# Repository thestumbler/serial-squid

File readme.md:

## Synopsis

The Serial Squid is a serial communications hub, useful for the development and testing of embedded systems projects. It can be operated stand-alone or remotely. True to its namesake, the Serial Squid has eight arms, two tentacles, and a round body. The I/O ports are found on the appendages, and the user interface and other supporting circuitry is found on the head and main body.

More information about the project can be found on my blog and project pages.

* [thestumbler](http://thestumbler.github.io)
* [theserialsquid](http://thestumbler.github.io/serial-squid/)

## Project File Organization

#### Key Files of Interest

* Bill of Materials:  docs/squid-bom.ods / .xlsx
* Block Diagram: docs/squid-block-diag.odg / .pdf
* LPC1769 Pinout Chart:  docs/squid-pinouts.ods / .xlsx
* Mechanical Drawing: mech/pcb_squid.dwg
* Parts Datasheets: parts/
* KiCAD Schematics, PCB files: sch/

## Status

* BOM is 98% completed.  All parts can be procured from DigiKey.  One problem has been sourcing a SMT 2x3 shrouded box header.

* Schematics 98% completed.  A few minor changes to be made, have been postponed until preliminary routing of the board is completed.  I want to see how much free room is remaining before deciding on the final few schematic changes.

* PCB first draft parts placement completed.  Routing will start after one more pass over the placement.

## github TODO

Add OpenSCAD 3D source code, which gives an fairly realistic mock-up of the final assembly.  It all works, but I need to re-organize some modules.  For example, many non-header parts reside in the header module.  Also, I need to sort out how to make a fork of another project, since I built my OpenSCAD library of parts upon a pre-existing library.

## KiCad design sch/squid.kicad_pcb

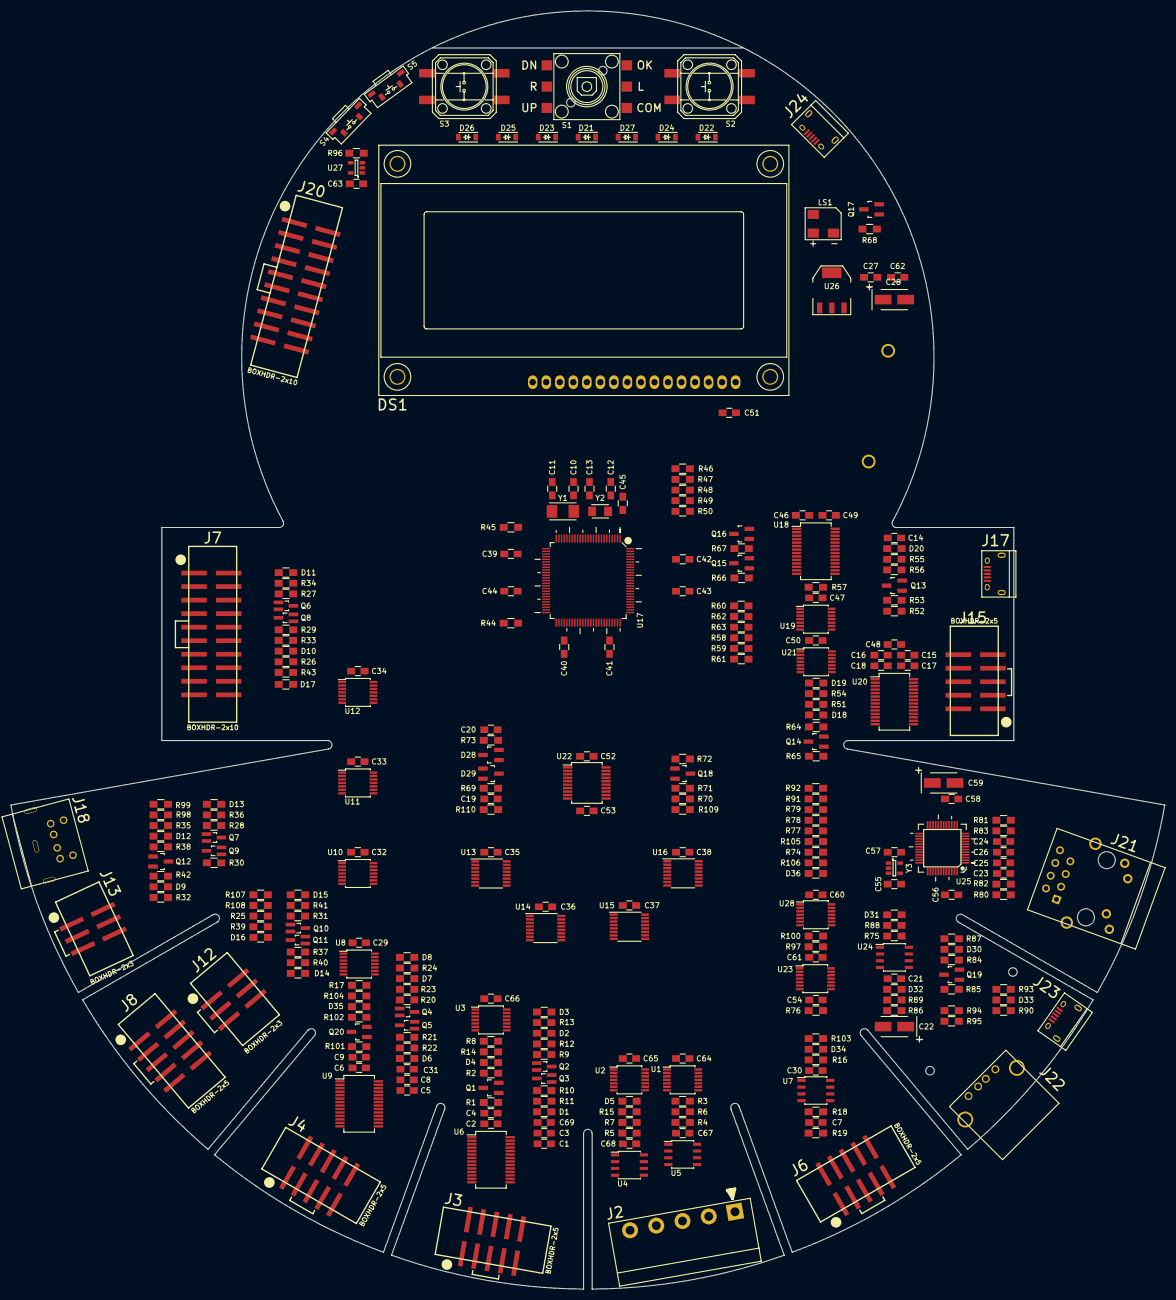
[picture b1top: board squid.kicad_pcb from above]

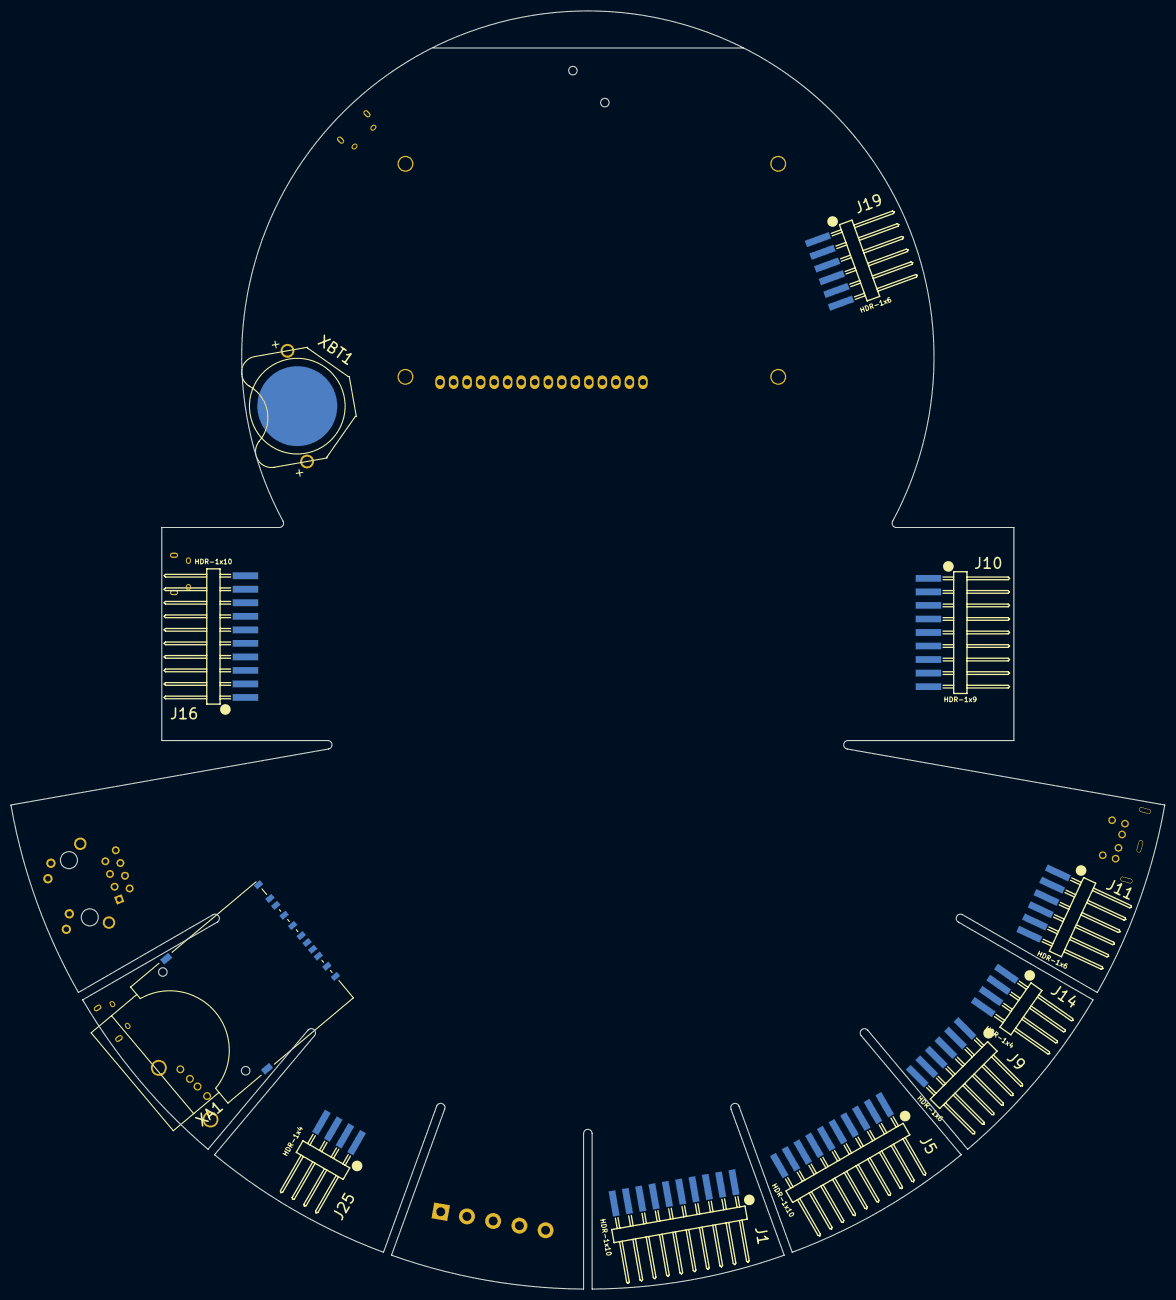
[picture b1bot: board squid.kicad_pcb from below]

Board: 2 copper layers, 216.7 x 240.0 mm, 300 parts (11 on the bottom side), 278 nets, no tracks yet.

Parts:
C1, C2, C3, C4, C5, C6, C8, C9, C14, C15, C16, C17, C18, C21, C23, C24, C25, C26, C29, C30, C31, C32, C33, C34, C35, C36, C37, C38, C40, C41, C42, C43, C44, C45, C46, C47, C48, C49, C50, C51, C52, C53, C54, C55, C56, C57, C58, C60, C61, C62, C63, C64, C65, C66, C67, C68, C69: 0.1uF; C_0805_HandSoldering
C7: 0.001uF; C_0805_HandSoldering
C10, C11, C12, C13: 18pF; C_0805_HandSoldering
C19, C20: 0.47uF; C_0805_HandSoldering
C22, C28, C59: 10uF; TantalC_SizeB_EIA-3528_HandSoldering
C27, C39: 1.0uF; C_0805_HandSoldering
D1, D2, D3, D4, D5, D6, D7, D8, D9, D10, D11, D12, D13, D14, D15, D16, D17, D18, D19, D20, D30, D31, D32, D33, D34, D35, D36: LED-GREEN; R_0805_HandSoldering
D21, D22, D23, D24, D25, D26, D27: 1N4148; SOD-123
D28, D29: BAT54; SOT-23_Handsoldering
DS1: LCD-4x20; NHD-0420AZ
J1, J5, J16: HDR-1x10; PHDR-RA-SMT-1x10
J2: TERM-BLOCK-5; term-block-5
J3, J4, J6, J8, J15: BOXHDR-2x5; SHDR-SMT-2x5
J7, J20: BOXHDR-2x10; SHDR-SMT-2x10
J9, J11, J19: HDR-1x6; PHDR-RA-SMT-1x6
J10: HDR-1x9; PHDR-RA-SMT-1x9
J12, J13: BOXHDR-2x3; SHDR-SMT-2x3
J14, J25: HDR-1x4; PHDR-RA-SMT-1x4
J17, J23, J24: USB-MICRO-B; USB_Micro-B
J18: MINIDIN6; MINIDIN-RA-THRU-6
J21: RJ45-MAGS; RJ45_TRANSFO_PULSE_A
J22: USB-TYPE-A; USB_A
LS1: BUZZER; BUZZER-CSS-0575A
Q1, Q12, Q13, Q14, Q15, Q16, Q17, Q20: 2N3904; SOT-23-BEC-HAND
Q2, Q3, Q4, Q5, Q6, Q7, Q8, Q9, Q10, Q11: DMG1013; SOT-323-GSD-HAND
Q18: 2N2222; SOT-23-BEC-HAND
Q19: 2N3906; SOT-23-BEC-HAND
R1, R38, R56, R65, R66, R67, R68, R72, R73, R84, R101: 1K; R_0805_HandSoldering
R2, R3, R4, R5, R6, R7, R8, R9, R10, R16, R17, R20, R21, R25, R26, R27, R28, R29, R30, R31, R37, R44, R45, R46, R47, R48, R49, R50, R53, R57, R58, R59, R60, R61, R62, R63, R64, R69, R70, R71, R74, R75, R76, R77, R78, R79, R96, R97, R100, R102, R105: 10K; R_0805_HandSoldering
R11, R12, R13, R14, R15, R22, R23, R24, R32, R33, R34, R35, R36, R39, R40, R41, R43, R51, R54, R55, R87, R88, R89, R90, R91, R92, R93, R103, R104, R106: 220; R_0805_HandSoldering
R18, R19: 60; R_0805_HandSoldering
R42: 20K; R_0805_HandSoldering
R52, R98, R99, R107, R108, R109, R110: 4.7K; R_0805_HandSoldering
R80, R81, R82, R83: 49.9; R_0805_HandSoldering
R85: 1.5K; R_0805_HandSoldering
R86: 100K; R_0805_HandSoldering
R94, R95: 15K; R_0805_HandSoldering
S1: SW_NAVI; SW_NAVI_JS5208
S2, S3: SW_PUSH; SW_PBUTTON_TL330
S4, S5: SW_PUSH_RA; SW_SPSW_TACT_RA
U1, U2, U3, U8, U10, U11, U12, U19, U21, U23, U28: 74HCT4066; TSSOP-14_4.4x5mm_Pitch0.65mm
U4, U5: SN75176B; SOIC-8_3.9x4.9mm_Pitch1.27mm
U6, U9, U20: MAX3241E; SSOP-28_5.3x10.2mm_Pitch0.65mm
U7: TJA1040; SOIC-8_3.9x4.9mm_Pitch1.27mm
U13, U14, U15, U16: 74HCT595; TSSOP-16_4.4x5mm_Pitch0.65mm
U17: LPC1769; LQFP-100_14x14mm_Pitch0.5mm
U18: FT232R; SSOP-28_5.3x10.2mm_Pitch0.65mm
U22: PIC16F1847; SSOP-20_5.3x7.2mm_Pitch0.65mm
U24: LM3526-L; SOIC-8_3.9x4.9mm_Pitch1.27mm
U25: DP83848; PQFP48-14x14mm
U26: MIC39100-3.3; SOT-223
U27: MCP1322; SOT-23-5
XA1: SD-SOCKET; SD_Card_Receptacle
XBT1: CR2032-SOCKET; SOCKET-SMT-CR2032-KEYSTONE-3003
Y1: 12MHz; Crystal_SMD_5032_2Pads
Y2: 32.768KHz; Crystal_SMD_3215_2Pads
Y3: 50MHz; SOT-23-5

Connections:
+3V3: C23.1, C24.1, C28.1, C31.2, C39.1, C40.1, C41.1, C42.1, C43.1, C44.1, C45.1, C46.2, C48.1, C52.1, C53.2, C55.1, C56.2, C57.2, C58.1, C59.1, C60.1, C61.1, C62.1, C63.1, C69.2, D2.2, D7.2, D11.2, D13.2, D15.2, D29.2, J20.1, J20.2, Q2.S, Q4.S, Q6.S, Q7.S, Q10.S, R2.1, R4.1, R9.1, R20.1, R27.1, R28.1, R31.1, R44.1, R45.1, R47.1, R48.1, R49.1, R50.1, R58.1, R59.1, R60.1, R61.1, R62.1, R63.1, R64.1, R69.1, R74.2, R77.2, R78.2, R79.2, R80.1, R81.1, R82.2, R83.2, R91.2, R92.2, R96.1, R97.1, R98.1, R99.1, R100.1, R102.1, R105.2, R109.1, R110.1, U6.26, U9.26, U17.10, U17.28, U17.42, U17.54, U17.71, U17.84, U17.96, U18.4, U20.26, U22.15, U22.16, U25.22, U25.32, U25.48, U26.3, U27.5, U28.14, XA1.4, Y3.4
+5V: C21.1, C27.1, C29.1, C30.2, C32.1, C33.1, C34.1, C35.1, C36.1, C37.1, C38.1, C47.1, C49.1, C50.1, C51.2, C54.1, C64.1, C65.1, C66.1, C67.1, C68.1, D1.2, D6.2, D10.2, D12.2, D14.2, D34.2, DS1.2, DS1.15, J6.8, J18.4, J24.1, J25.1, LS1.1, Q3.S, Q5.S, Q8.S, Q9.S, Q11.S, Q19.E, R10.1, R16.2, R21.1, R29.1, R30.1, R37.1, U1.14, U2.14, U3.14, U4.8, U5.8, U7.3, U8.14, U10.14, U11.14, U12.14, U13.16, U14.16, U15.16, U16.16, U18.20, U19.14, U21.14, U23.14, U24.7, U26.1
/CFG0: R55.2, R56.2, U13.15
/CFG1: R51.2, R65.1, U13.1, U20.22
/CFG2: R54.2, R57.1, U13.2, U19.5, U19.6, U19.12, U19.13, U21.5, U21.13
/CFG3: R1.1, R14.2, U6.22, U13.3
/CFG4: R3.1, R15.2, U1.5, U1.13, U2.6, U13.4
/CFG5: R8.1, R13.2, U2.5, U2.13, U3.5, U3.6, U3.12, U3.13, U13.5
/CFG6: Q3.G, R10.2, R11.2, U13.6
/CFG7: Q2.G, R9.2, R12.2, U13.7, U14.14
/CFG8: R101.1, R104.2, U9.22, U14.15
/CFG9: R17.1, R24.2, U8.5, U8.6, U8.12, U8.13, U14.1
/CFG10: Q5.G, R21.2, R22.2, U14.2
/CFG11: Q4.G, R20.2, R23.2, U14.3
/CFG12: R16.1, R103.2, U7.8, U14.4
/CFG13: R25.1, R39.2, U10.5, U10.6, U10.12, U10.13, U11.5, U11.13, U14.5
/CFG14: Q11.G, R37.2, R40.2, U14.6
/CFG15: Q10.G, R31.2, R41.2, U14.7, U15.14
/CFG16: R26.1, R43.2, U11.6, U11.12, U12.5, U12.6, U12.12, U12.13, U15.15
/CFG17: Q8.G, R29.2, R33.2, U15.1
/CFG18: Q6.G, R27.2, R34.2, U15.2
/CFG19: R32.2, U15.3
/CFG20: Q9.G, R30.2, R35.2, U15.4
/CFG21: Q7.G, R28.2, R36.2, U15.5
/CFG22: R75.2, R88.2, U15.6, U23.5, U23.13
/CFG23: R76.2, R87.2, U15.7, U16.14, U23.6, U23.12
/CFG24: R105.1, U16.15, U25.29
/CFG25: R74.1, R106.2, U16.1, U25.7, Y3.3
/CFG26: U16.2, U28.13
/CFG27: U16.3, U28.5
/COM0/COM0B_CTS: J15.6, U20.11
/COM0/COM0B_DSR: J15.2, U20.9
/COM0/COM0B_DTR: J15.7, U20.6
/COM0/COM0B_RTS: J15.4, U20.4
/COM0/COM0B_RXD: J15.3, U20.10
/COM0/COM0B_TXD: J15.5, U20.5
/COM0/COM0C_CTSL: J16.9, U21.3
/COM0/COM0C_DSR: J16.8, U21.1
/COM0/COM0C_DTR: J16.3, U19.3
/COM0/COM0C_RTSL: J16.2, U19.1
/COM0/COM0C_RXDL: J16.7, U19.10
/COM0/COM0C_TXD: J16.4, U19.8
/COM0/COM0_CTSL: R60.2, U17.81, U18.11, U20.12, U21.4
/COM0/COM0_DSR: R62.2, U17.59, U18.9, U20.14, U21.2
/COM0/COM0_DTR: R63.2, R67.2, U17.58, U18.2, U19.4, U20.17
/COM0/COM0_RTSL: R61.2, R66.2, U17.80, U18.3, U19.2, U20.19
/COM0/COM0_RXDL: R58.2, U17.98, U18.5, U19.11, U20.13
/COM0/COM0_TXDL: R59.2, U17.99, U18.1, U19.9, U20.18
/COM0/~RESET: C19.1, D28.1, J20.15, Q16.C, R45.2, R69.2, U17.17, U27.1
/COM1/COM1C_CTSL: J1.9, U3.4
/COM1/COM1C_DSR: J1.8, U3.2
/COM1/COM1C_DTR: J1.3, U2.4
/COM1/COM1C_RTSL: J1.2, U2.2
/COM1/COM1C_RXDL: J1.7, U3.11
/COM1/COM1C_TXD: J1.4, U3.9
/COM1/COM1_CTSL: U3.3, U6.16, U17.73
/COM1/COM1_DCDL: U6.19, U17.70
/COM1/COM1_DSRL: U3.1, U6.18, U17.69
/COM1/COM1_DTRL: U2.3, U2.9, U6.12, U17.68
/COM1/COM1_RIL: U6.15, U17.67
/COM1/COM1_RTSL: U1.2, U1.3, U2.1, U6.14, U17.66
/COM1/COM1_RXDL: U3.10, U5.1, U6.17, U17.74
/COM1/COM1_TXDL: R7.1, U3.8, U4.4, U5.4, U6.13, U17.75
/COM1/RXA: J2.3, U4.7
/COM1/RXB: J2.4, U4.6
/COM1/TXA: J2.1, U5.7
/COM1/TXB: J2.2, U5.6
/COM2-CAN/CAN_RD: U7.4, U17.46
/COM2-CAN/CAN_TD: U7.1, U17.47
/COM2-CAN/COM2B_CTSL: J5.9, U8.11
/COM2-CAN/COM2B_RTSL: J5.2, U8.1
/COM2-CAN/COM2B_RXDL: J5.7, U8.9
/COM2-CAN/COM2B_TXD: J5.4, U8.3
/COM2-CAN/COM2_CTSL: U8.10, U9.16, U17.57
/COM2-CAN/COM2_RTSL: U8.2, U9.14, U17.56
/COM2-CAN/COM2_RXDL: U8.8, U9.17, U17.64
/COM2-CAN/COM2_TXDL: U8.4, U9.13, U17.65
/COM3, PROG/COM3_MISO: J8.7, J12.1, U10.8, U10.9, U12.8, U17.61
/COM3, PROG/COM3_MOSI: J8.8, J12.4, U10.10, U10.11, U12.3, U17.60
/COM3, PROG/COM3_SCL: J8.5, J9.1, J9.5, R108.2, U10.1, U10.2, U12.1, U17.24
/COM3, PROG/COM3_SCLK: J8.9, J12.3, U11.1, U11.2, U11.10, U17.62
/COM3, PROG/COM3_SDA: J8.6, J9.2, J9.6, R107.2, U10.3, U10.4, U12.10, U17.25
/COM3, PROG/ISP_MISO: J13.1, U17.37
/COM3, PROG/ISP_MOSI: J11.4, J13.4, U17.38
/COM3, PROG/ISP_SCLK: J11.5, J13.3, U17.34
/COM3, PROG/ISP_VDD: J11.2, J13.2, Q7.D, Q9.D, R42.2
/COM3, PROG/ISP_VPP_~MCLR: J11.1, Q12.C, R42.1
/COM3, PROG/TCK: J7.9, J10.4, U11.11
/COM3, PROG/TDI: J7.5, J10.7, U12.4
/COM3, PROG/TDO: J7.13, J10.6, U12.9
/COM3, PROG/TMS: J7.7, J10.9, U11.9
/COM3, PROG/~COM3_SSEL: J8.10, J12.5, U11.3, U11.4, U11.8, U17.63
/COM3, PROG/~ISP_SSEL: J13.5, R38.1, U17.35
/COM3, PROG/~SRST: J7.15, U12.11
/COM3, PROG/~TRST: J7.3, U12.2
/CONFIG/SHIFT_CLK: R70.1, U13.11, U14.11, U15.11, U16.11
/CONFIG/SHIFT_IN: R71.1, U13.14
/CONFIG/SHIFT_LOAD: U13.12, U14.12, U15.12, U16.12, U22.19
/CONFIG/SHIFT_OUT: U16.9, U22.12
/CONFIG/~SHIFT_OE: U13.13, U14.13, U15.13, U16.13, U22.20
/CONFIG/~SHIFT_RESET: U13.10, U14.10, U15.10, U16.10, U22.17
/CPU/BOOT_ISP: Q15.C, R44.2, S5.1, U17.53, U22.18
/CPU/COM3_RXD: J8.3, J14.4, U17.6
/CPU/COM3_TXD: J8.4, J14.1, U17.7
/CPU/CONFIG_SCL: R109.2, U17.49, U22.11
/CPU/CONFIG_SDA: R110.2, U17.48, U22.8
/CPU/DISP_DB0: DS1.11, U17.32
/CPU/DISP_DB1: DS1.12, U17.44
/CPU/DISP_DB2: DS1.13, U17.45
/CPU/DISP_DB3: DS1.14, U17.20
/CPU/DISP_OP_ENA: DS1.6, U17.26
/CPU/DISP_REGSEL: DS1.4, U17.85
/CPU/DISP_RW: DS1.5, U17.82
/CPU/LAN_CRS: U17.92, U25.40
/CPU/LAN_MDC: U17.87, U25.31
/CPU/LAN_MDIO: U17.86, U25.30
/CPU/LAN_REF_CLK: U17.88, U25.34, Y3.5
/CPU/LAN_RXD0: U17.91, U25.43
/CPU/LAN_RXD1: U17.90, U25.44
/CPU/LAN_RXER: U17.89, U25.41
/CPU/LAN_TXD0: U17.95, U25.3
/CPU/LAN_TXD1: U17.94, U25.4
/CPU/LAN_TXEN: U17.93, U25.2
/CPU/MSD_MISO: U17.77, XA1.7
/CPU/MSD_MOSI: U17.76, XA1.2
/CPU/MSD_SCLK: U17.78, XA1.5
/CPU/PBCOL_SEN0: D26.1, D27.1, U17.9
/CPU/PBCOL_SEN1: D24.1, D25.1, U17.52
/CPU/PBCOL_SEN2: D22.1, D23.1, U17.51
/CPU/PBCOL_SEN3: D21.1, U17.50
/CPU/PBROW_DRV0: S1.1, U17.39
/CPU/PBROW_DRV1: S2.1, S3.1, U17.40
/CPU/RTCK: J20.11, U17.100
/CPU/TCK: J20.9, R46.1, U17.5
/CPU/TDI: J20.5, R49.2, U17.2
/CPU/TDO: J20.13, R50.2, U17.1
/CPU/TMS: J20.7, R48.2, U17.3
/CPU/USB_CONNECT: R84.2, U17.8
/CPU/USB_DM: U17.30, U23.1, U23.8
/CPU/USB_DP: U17.29, U23.3, U23.10
/CPU/USB_OVRCR: U17.43, U24.2
/CPU/USB_PWRD: C22.1, D32.2, J22.1, R86.2, U17.36, U24.8
/CPU/USB_VBUS: R93.1, U17.21
/CPU/VBATT: U17.19, XBT1.1
/CPU/~MSD_SENSE: R97.2, R100.2, U17.27, U28.2, U28.3
/CPU/~MSD_SSEL: U17.79, XA1.1
/CPU/~TRST: J20.3, R47.2, U17.4
/CPU/~USB_PPWR: U17.33, U24.1
/PIC-SQPROG/DISP_BACKL: DS1.16, Q18.C
/PIC-SQPROG/DISP_CONTR: C20.1, DS1.3, R73.1
/PIC-SQPROG/ICSP_CLK: J19.5, R70.2, U22.13
/PIC-SQPROG/ICSP_DAT: J19.4, R71.2, U22.14
/PIC-SQPROG/ICSP_MCLR: D28.2, J19.1, U22.4
/PIC-SQPROG/PS2_CLK: J18.5, R99.2, U22.7
/PIC-SQPROG/PS2_DAT: J18.1, R98.2, U22.9
/USB-LAN/USBD_DM: J23.2, U23.9
/USB-LAN/USBD_DP: J23.3, R85.1, U23.11
/USB-LAN/USBH_DM: J22.2, R94.2, U23.2
/USB-LAN/USBH_DP: J22.3, R95.2, U23.4
/USER/BUZZ: R68.2, U22.10
GND: C3.1, C4.1, C7.2, C8.1, C9.1, C10.2, C11.2, C12.2, C13.2, C14.1, C15.2, C16.2, C19.2, C20.2, C21.2, C22.2, C23.2, C24.2, C25.2, C26.2, C27.2, C28.2, C29.2, C30.1, C31.1, C32.2, C33.2, C34.2, C35.2, C36.2, C37.2, C38.2, C39.2, C40.2, C41.2, C42.2, C43.2, C44.2, C45.2, C46.1, C47.2, C48.2, C49.2, C50.2, C51.1, C52.2, C53.1, C54.2, C55.2, C56.1, C57.1, C58.2, C59.2, C60.2, C61.2, C62.2, C63.2, C64.2, C65.2, C66.2, C67.2, C68.2, C69.1, D3.1, D4.1, D5.1, D8.1, D9.1, D16.1, D17.1, D18.1, D19.1, D20.1, D30.1, D31.1, D35.1, D36.1, DS1.1, J1.5, J1.6, J2.5, J3.9, J4.9, J5.5, J5.6, J7.4, J7.6, J7.8, J7.10, J7.12, J7.14, J7.16, J7.18, J7.20, J8.2, J9.4, J10.2, J11.3, J12.6, J13.6, J14.2, J14.3, J15.9, J16.5, J16.6, J17.5, J17.6, J18.3, J18.7, J18.8, J18.9, J19.3, J20.4, J20.6, J20.8, J20.10, J20.12, J20.14, J20.16, J20.18, J20.20, J21.8, J21.13, J21.14, J22.4, J22.5, J23.5, J23.6, J24.5, J24.6, Q1.E, Q12.E, Q13.E, Q14.E, Q15.E, Q16.E, Q17.E, Q18.E, Q20.E, R3.2, R5.2, R6.2, R7.2, R8.2, R17.2, R25.2, R26.2, R46.2, R53.2, R57.2, R75.1, R76.1, R86.1, R89.1, R90.1, R94.1, R95.1, S4.1, S5.2, U1.7, U2.7, U3.7, U4.5, U5.5, U6.25, U7.2, U8.7, U9.25, U10.7, U11.7, U12.7, U13.8, U14.8, U15.8, U16.8, U17.11, U17.31, U17.41, U17.55, U17.72, U17.83, U17.97, U18.7, U18.18, U18.21, U18.25, U18.26, U19.7, U20.25, U21.7, U22.5, U22.6, U23.7, U24.6, U25.15, U25.19, U25.35, U25.36, U25.47, U26.2, U27.2, U28.7, XA1.3, XA1.6, XA1.12, XA1.13, XBT1.2, Y3.1
unnamed: C1.1, U6.28
unnamed: C1.2, U6.24
unnamed: C2.1, U6.1
unnamed: C2.2, U6.2
unnamed: C3.2, U6.27
unnamed: C4.2, U6.3
unnamed: C5.1, U9.28
unnamed: C5.2, U9.24
unnamed: C6.1, U9.1
unnamed: C6.2, U9.2
unnamed: C7.1, R18.1, R19.1, U7.5
unnamed: C8.2, U9.27
unnamed: C9.2, U9.3
unnamed: C10.1, U17.22, Y1.1
unnamed: C11.1, U17.23, Y1.2
unnamed: C12.1, U17.16, Y2.1
unnamed: C13.1, U17.18, Y2.2
unnamed: C14.2, U18.17
unnamed: C15.1, U20.27
unnamed: C16.1, U20.3
unnamed: C17.1, U20.24
unnamed: C17.2, U20.28
unnamed: C18.1, U20.2
unnamed: C18.2, U20.1
unnamed: C25.1, J21.4
unnamed: C26.1, J21.5
unnamed: D1.1, R11.1
unnamed: D2.1, R12.1
unnamed: D3.2, R13.1
unnamed: D4.2, R14.1
unnamed: D5.2, R15.1
unnamed: D6.1, R22.1
unnamed: D7.1, R23.1
unnamed: D8.2, R24.1
unnamed: D9.2, R32.1
unnamed: D10.1, R33.1
unnamed: D11.1, R34.1
unnamed: D12.1, R35.1
unnamed: D13.1, R36.1
unnamed: D14.1, R40.1
unnamed: D15.1, R41.1
unnamed: D16.2, R39.1
unnamed: D17.2, R43.1
unnamed: D18.2, R51.1
unnamed: D19.2, R54.1
unnamed: D20.2, R55.1
unnamed: D21.2, S1.4
unnamed: D22.2, S2.2
unnamed: D23.2, S1.5
unnamed: D24.2, S1.3
unnamed: D25.2, S1.6
unnamed: D26.2, S3.2
unnamed: D27.2, S1.2
unnamed: D29.1, J19.2
unnamed: D30.2, R87.1
unnamed: D31.2, R88.1
unnamed: D32.1, R89.2
unnamed: D33.1, R90.2
unnamed: D33.2, J23.1, R93.2
unnamed: D34.1, R103.1
unnamed: D35.2, R104.1
unnamed: D36.2, R106.1
unnamed: J1.1, J1.10, Q2.D, Q3.D
unnamed: J3.1, U6.4
unnamed: J3.2, U6.5
unnamed: J3.3, U6.6
unnamed: J3.4, U6.9
unnamed: J3.5, U6.10
unnamed: J3.6, U6.7
unnamed: J3.7, U6.11
unnamed: J3.8, U6.8
unnamed: J4.3, U9.6
unnamed: J4.4, U9.9
unnamed: J4.5, U9.10
unnamed: J4.6, U9.7
unnamed: J5.1, J5.10, Q4.D, Q5.D
unnamed: J7.1, J7.2, J10.1, Q6.D, Q8.D
unnamed: J8.1, J9.3, J12.2, Q10.D, Q11.D, R107.1, R108.1
unnamed: J17.1, R52.2
unnamed: J17.2, U18.16
unnamed: J17.3, U18.15
unnamed: J21.1, R80.2, U25.17
unnamed: J21.2, R82.1, U25.16
unnamed: J21.3, R83.1, U25.14
unnamed: J21.6, R81.2, U25.13
unnamed: J21.9, R91.1
unnamed: J21.10, R77.1, U25.28
unnamed: J21.11, R92.1
unnamed: J21.12, R79.1, U25.26
unnamed: J6.4, J25.2, R18.2, U7.7
unnamed: J6.3, J25.3, R19.2, U7.6
unnamed: J6.2, J6.5, J6.9, J25.4
unnamed: LS1.2, Q17.C
unnamed: Q1.B, R1.2
unnamed: Q1.C, R2.2, U6.23
unnamed: Q12.B, R38.2
unnamed: Q13.B, R56.1
unnamed: Q13.C, R52.1, R53.1, U18.19
unnamed: Q14.B, R65.2
unnamed: Q14.C, R64.2, U20.23
unnamed: Q15.B, R66.1
unnamed: Q16.B, R67.1
unnamed: Q17.B, R68.1
unnamed: Q18.B, R72.1
unnamed: Q19.B, R84.1
unnamed: Q19.C, R85.2
unnamed: Q20.B, R101.2
unnamed: Q20.C, R102.2, U9.23
unnamed: R4.2, U1.4, U5.2
unnamed: R5.1, U2.8, U4.3
unnamed: R6.1, U1.1, U5.3
unnamed: R72.2, U22.2
unnamed: R73.2, U22.3
unnamed: R78.1, U25.27
unnamed: R96.2, S4.2, U27.4
unnamed: U28.1, XA1.10
unnamed: U28.4, XA1.11

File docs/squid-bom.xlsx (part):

SERIAL SQUID BOM
42492
 |  |  |  |  |  |  |  |  |  |  |  |  |  |  |  |  |  |  |  |  |  | 165.55999999999995 | 1384.6600000000008 | 6410.3499999999985 | 10859.15 | 46244.47 | 83534.299999999988
 |  |  |  |  |  |  |  |  |  |  |  |  |  |  |  |  |  |  |  |  |  | 165.55999999999995 | 138.46600000000007 | 128.20699999999997 | 108.5915 | 92.488939999999999 | 83.534299999999988
 |  |  |  |  |  |  |  |  |  |  |  |  |  |  |  |  |  |  |  |  |  | 1 | 10 | 50 | 100 | 500 | 1000
ITEM | QTY | REF-DES | CODE | TYPE | MANUFACTURER | PART-NUMBER | VALUE | PACKAGE | MFR-PACKAGE | DESCRIPTION | REMARKS | VENDOR | VENDOR-PN | VENDOR-STOCK | UNIT-PR-1 | UNIT-PR-10 | UNIT-PR-50 | UNIT-PR-100 | UNIT-PR-500 | UNIT-PR-1000 |  | EXT-PR-1 | EXT-PR-10 | EXT-PR-50 | EXT-PR-100 | EXT-PR-500 | EXT-PR-1000
1 | 1 | U17 | IC | SMT | NXP SEMICONDUCTOR | LPC1769FBD100 | LPC1769 | LQFP100 | SOT407-1 | IC, MCU, ARM Cortex-M3, 120MHZ, 512KB FLASH, 64KB RAM | @mcu | Digikey | 568-4966-ND | 2727 | 11.19 | 10.105 | 10.105 | 8.3659999999999997 | 7.2850000000000001 | 6.3449999999999998 |  | 11.19 | 10.105 | 10.105 | 8.3659999999999997 | 7.2850000000000001 | 6.3449999999999998
2 | 1 | U22 | IC | SMT | MICROCHIP | PIC16F1847-I/SS | PIC16F1847 | SSOP20 | SSOP20 | IC, MCU, PIC 8-bit, 32MHz, 14KB FLASH, 1KB RAM, 256B EEPROM | @mcu | Digikey | PIC16F1847-I/SS-ND | 1121 | 1.5 | 1.5 | 1.38 | 1.25 | 1.25 | 1.25 |  | 1.5 | 1.5 | 1.38 | 1.25 | 1.25 | 1.25
3 | 1 | U27 | IC | SMT | MICROCHIP | MCP1322T-29LE/OT | MCP1322 | SOT23-5 | SOT23-5 | IC, Voltage Supervisor w/Reset Input | @mcu | Digikey | MCP1322T-29LE/OTCT-ND | 2246 | 0.59 | 0.59 | 0.49 | 0.45 | 0.45 | 0.45 |  | 0.59 | 0.59 | 0.49 | 0.45 | 0.45 | 0.45
4 | 1 | U25 | IC | SMT | TEXAS INSTRUMENTS | DP83848CVV/NOPB | DP83848 | LQFP48 | PT48 | IC, Ethernet 10/100 Mb/s Physical Layer Interface | @lan | Digikey | DP83848CVVX/NOPBCT-ND | 15391 | 5.28 | 4.7409999999999997 | 4.7409999999999997 | 3.8894000000000002 | 3.3088600000000001 | 2.4187500000000002 |  | 5.28 | 4.7409999999999997 | 4.7409999999999997 | 3.8894000000000002 | 3.3088600000000001 | 2.4187500000000002
5 | 1 | U18 | IC | SMT | FUTURE TECHNOLOGY | FT232RL | FT232R | SSOP28 | SSOP28 | IC, USB to Serial UART Interface | @com0 @com1 | Digikey | 768-1007-1-ND | 145278 | 4.5 | 4.05 | 3.85 | 3.65 | 2.85 | 2.85 |  | 4.5 | 4.05 | 3.85 | 3.65 | 2.85 | 2.85
6 | 3 | U6,U9,U20 | IC | SMT | MAXIM | MAX3241ECAI+ | MAX3241E | SSOP28 | A28+1 | IC, Transceiver, RS-232, 2 Xmtr, 3 Rvcr | @com0, @com1, @com2 | Digikey | MAX3241ECAI+-ND | 889 | 6.83 | 6.4889999999999999 | 5.8521999999999998 | 5.8521999999999998 | 5.8521999999999998 | 5.8521999999999998 |  | 20.490000000000002 | 19.466999999999999 | 17.5566 | 17.5566 | 17.5566 | 17.5566
7 | 2 | U4,U5 | IC | SMT | TEXAS INSTRUMENTS | DS75176BM/NOPB | SN75176B | SOIC8-150 | D8 | IC, Transceiver, RS-422, w/Enables | @com1 | Digikey | DS75176BMX/NOPBCT-ND | 22832 | 1.41 | 1.2649999999999999 | 1.2649999999999999 | 0.9859 | 0.81535999999999997 | 0.64448000000000005 |  | 2.82 | 2.5299999999999998 | 2.5299999999999998 | 1.9718 | 1.6307199999999999 | 1.2889600000000001
8 | 1 | U7 | IC | SMT | NXP SEMICONDUCTOR | TJA1040T/CM | TJA1040 | SOIC8-150 | SOT96-1 | IC, XCVR, CAN, High-speed w/standby mode | @can | Digikey | 568-10289-1-ND | 29851 | 1.25 | 1.1140000000000001 | 1.1140000000000001 | 0.86839999999999995 | 0.71814 | 0.56791999999999998 |  | 1.25 | 1.1140000000000001 | 1.1140000000000001 | 0.86839999999999995 | 0.71814 | 0.56791999999999998
9 | 11 | U1-U3,U8,U10-U12,U19,U21,U23,U28 | IC | SMT | NXP SEMICONDUCTOR | 74HCT4066PW | 74HCT4066 | TSSOP14 | SOT402-1 | IC, CMOS Quad Bilateral Switch | @com0=2 @com1=3, @com2=1, @com3=1.5, @jtag=1.5, @usb=1, @sd=1 | Digikey | 568-8177-1-ND | 5280 | 0.45 | 0.36799999999999999 | 0.36799999999999999 | 0.25080000000000002 | 0.18772 | 0.1406 |  | 4.95 | 4.048 | 4.048 | 2.7588000000000004 | 2.0649199999999999 | 1.5466
10 | 4 | U13-U16 | IC | SMT | NXP SEMICONDUCTOR | 74HCT595PW | 74HCT595 | TSSOP16 | SOT403-1 | IC, Shift Register, 8-bit, Serial in, Serial and Parallel Out, w/Latches | @config | Digikey | 568-1561-1-ND | 23450 | 0.89 | 0.8 | 0.8 | 0.62380000000000002 | 0.51588000000000001 | 0.40795999999999999 |  | 3.56 | 3.2 | 3.2 | 2.4952000000000001 | 2.06352 | 1.63184
11 | 1 | U24 | IC | SMT | NATIONAL (TI) | LM3526M-L/NOPB | LM3526-L | SOIC8 | D8 | IC, USB HOST POWER SWITCH, OVER CURRENT PROTECTION | @usb | Digikey | LM3526M-L/NOPB-ND | 3049 | 1.9 | 1.704 | 1.704 | 1.3695999999999999 | 1.1252599999999999 | 0.93235000000000001 |  | 1.9 | 1.704 | 1.704 | 1.3695999999999999 | 1.1252599999999999 | 0.93235000000000001
12 | 1 | U26 | IC | SMT | MICREL (MICROCHIP) | MIC39100-3.3WS | MIC39100-3.3 | SOT-223 | SOT-223 | IC, VOLTAGE REGULATOR, LDO, 1A, 3.3V FIXED | @power | Digikey | 576-1172-ND | 4097 | 1.4 | 1.4 | 1.1599999999999999 | 1.06 | 1.06 | 1.06 |  | 1.4 | 1.4 | 1.1599999999999999 | 1.06 | 1.06 | 1.06
13 | 7 | D21-D27 | SEM | SMT | FAIRCHILD SEMI | MMBD4148 | 1N4148 | SOT-23 | SOT-23-3L | DIODE, SMALL SIGNAL, 1N4148, 200mA, 100V, SMD |  | Digikey | MMBD4148FSCT | 109221 | 0.19 | 0.17 | 0.17 | 9.2899999999999996E-2 | 5.7079999999999999E-2 | 3.8929999999999999E-2 |  | 1.33 | 1.1900000000000002 | 1.1900000000000002 | 0.65029999999999999 | 0.39955999999999997 | 0.27250999999999997
14 | 2 | D28,D29 | SEM | SMT | DIODES INC | BAT54-7-F | BAT54 | SOT-23 | SOT-23 | DIODE, SCHOTTKY, 200mA, 30V |  | Digikey | BAT54-FDICT-ND | 88219 | 0.15 | 0.13500000000000001 | 0.13500000000000001 | 7.3700000000000002E-2 | 4.53E-2 | 3.09E-2 |  | 0.3 | 0.27 | 0.27 | 0.1474 | 9.06E-2 | 6.1800000000000001E-2
15 | 27 | D1-D20,D30-D36 | SEM | SMT | LITE-ON | LTST-C170KGKT | LED-GREEN | EIA0805 | EIA0805 | LED, GREEN, SMT, TOP VIEW, 35mcd @ 20mA |  | Digikey | 160-1414-1-ND | 718943 | 0.38 | 0.29599999999999999 | 0.29599999999999999 | 0.16139999999999999 | 9.146E-2 | 6.9940000000000002E-2 |  | 10.26 | 7.992 | 7.992 | 4.3577999999999992 | 2.4694199999999999 | 1.8883800000000002
16 | 8 | Q1,Q12-Q17,Q20 | SEM | SMT | DIODES INC | MMBT3904-7-F | 2N3904 | SOT-23 | SOT-23 | TRANSISTOR, NPN, 2N3906, 40V @ 200mA, SMT |  | Digikey | MMBT3904-FDICT-ND | 588937 | 0.12 | 0.108 | 0.108 | 5.8999999999999997E-2 | 3.6240000000000001E-2 | 2.4719999999999999E-2 |  | 0.96 | 0.86399999999999999 | 0.86399999999999999 | 0.47199999999999998 | 0.28992000000000001 | 0.19775999999999999
17 | 1 | Q19 | SEM | SMT | DIODES INC | MMBT3906-7-F | 2N3906 | SOT-23 | SOT-23 | TRANSISTOR, PNP, 2N3906, 40V @ 200mA, SMT |  | Digikey | MMBT3906-FDICT-ND | 223756 | 0.12 | 0.108 | 0.108 | 5.8999999999999997E-2 | 3.6240000000000001E-2 | 2.4719999999999999E-2 |  | 0.12 | 0.108 | 0.108 | 5.8999999999999997E-2 | 3.6240000000000001E-2 | 2.4719999999999999E-2
18 | 1 | Q18 | SEM | SMT | DIODES INC | MMBT2222A-7-F | 2N2222 | SOT-23 | SOT-23 | TRANSISTOR, NPN, 2N2222A, 40V @ 600mA, SMT |  | Digikey | MMBT2222A-FDICT-ND | 476496 | 0.13 | 0.122 | 0.122 | 6.6299999999999998E-2 | 4.0779999999999997E-2 | 2.7810000000000001E-2 |  | 0.13 | 0.122 | 0.122 | 6.6299999999999998E-2 | 4.0779999999999997E-2 | 2.7810000000000001E-2
19 | 10 | Q2-Q11 | SEM | SMT | DIODES INC | DMG1013UW-7 | DMG1013 | SOT-323 | SOT-323 | TRANSISTOR, MOSFET, P-CHAN, 20V @ 800mA, SMT |  | Digikey | DMG1013UW-7DICT-ND | 61614 | 0.34 | 0.27 | 0.27 | 0.14680000000000001 | 9.6500000000000002E-2 | 6.5750000000000003E-2 |  | 3.4000000000000004 | 2.7 | 2.7 | 1.4680000000000002 | 0.96500000000000008 | 0.65749999999999997
20 | 1 | Y1 | OSC | SMT | CTS FREQUENCY | 445C35A12M00000 | 12.000MHZ | CTS-5x3.2 | CTS-5x3.2 | CRYSTAL, QUARTZ, 12.000 MHZ, 10pf LOAD, 50 OHM, SMD |  | Digikey | CTX1435CT-ND | 2000 | 0.66 | 0.55200000000000005 | 0.49559999999999998 | 0.441 | 0.42 | 0.42 |  | 0.66 | 0.55200000000000005 | 0.49559999999999998 | 0.441 | 0.42 | 0.42
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
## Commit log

2016-05-02 Baseline release
2016-05-23 Draft 1, PCB Preliminary Placement
2016-05-26 parts placement, draft 2, straight alignment
